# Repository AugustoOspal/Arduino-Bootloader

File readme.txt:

Comando para pull github.
Copiar las tres lineas y pegarlas en CMD

D:
cd "Pasantia 2021\Augusto Ospal\Arduino UNO bootloader"
git pull

Las hojas con los planos a imprimir de las plaquetas estan en cada una de las carpetas en las que corresponden

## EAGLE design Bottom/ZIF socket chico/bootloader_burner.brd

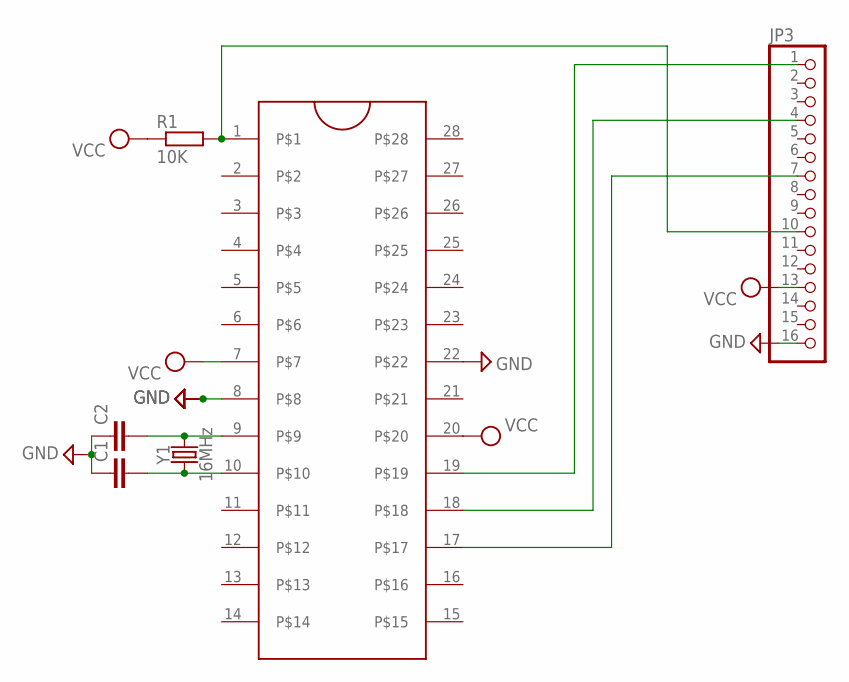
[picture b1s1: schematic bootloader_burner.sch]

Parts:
C1, C2: C-EU050-030X075; C050-030X075
J1: ZIFSOCKET-28-3"; DIL28-3-ZIF_SOCKET
JP3: PINHD-1X16; 1X16
R1: 10K; 0207/10
Y1: 16MHz; HC49US

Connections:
GND: C1.1, C2.1, J1.8, J1.22, JP3.16
unnamed: C2.2, J1.9, Y1.2
unnamed: C1.2, J1.10, Y1.1
PIN10ARDUINO: J1.1, JP3.10, R1.2
PIN11ARDUINO: J1.17, JP3.7
PIN12ARDUINO: J1.18, JP3.4
PIN13ARDUINO: J1.19, JP3.1
VCC: J1.7, J1.20, JP3.13, R1.1

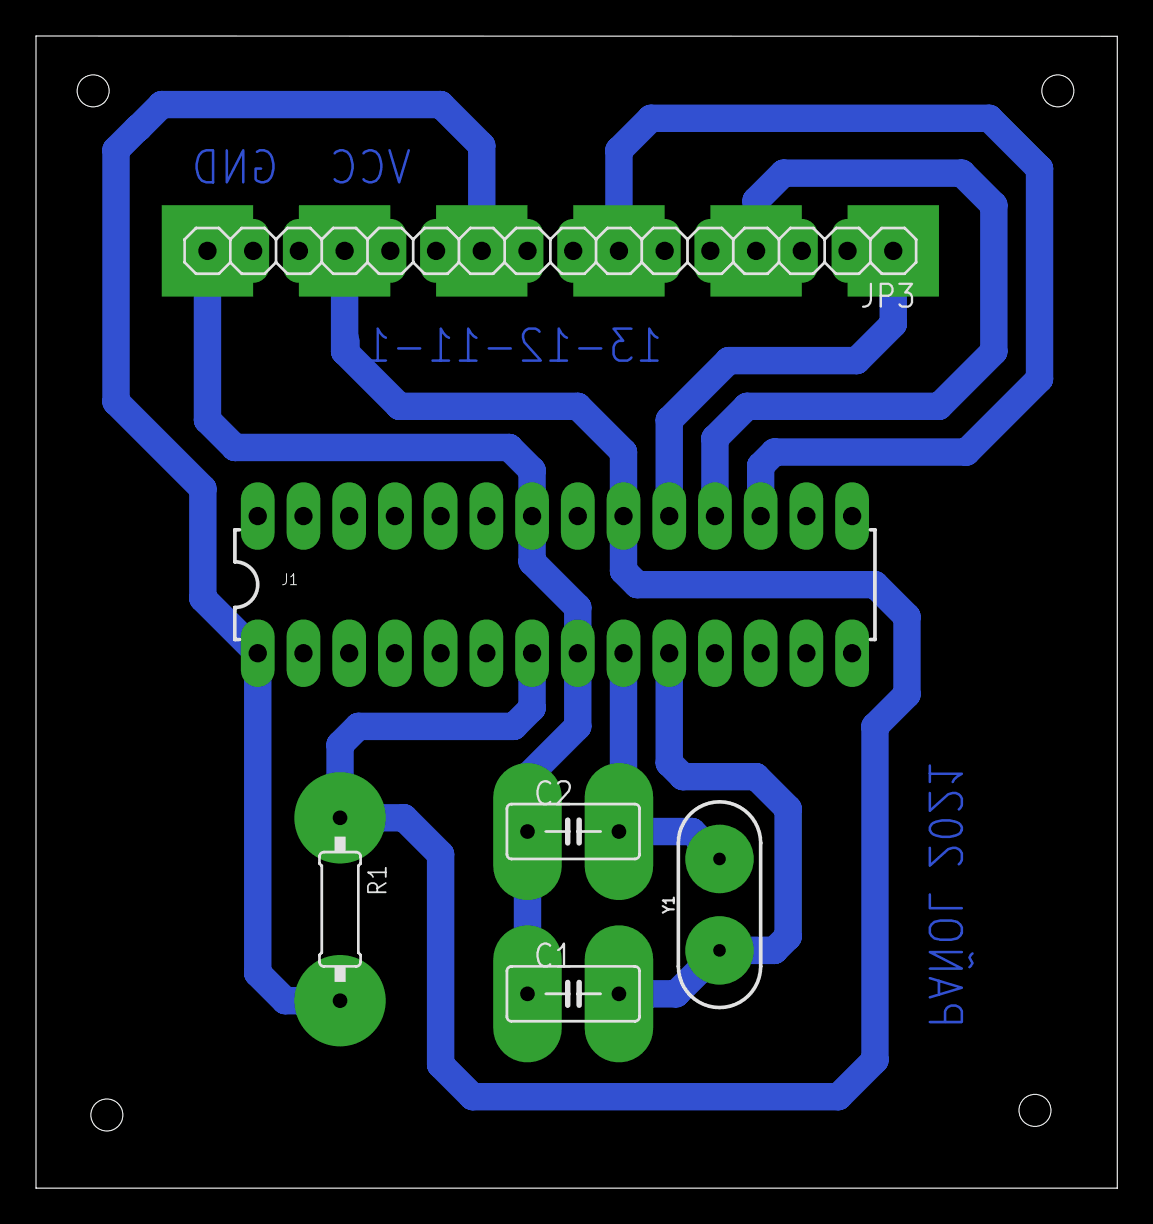
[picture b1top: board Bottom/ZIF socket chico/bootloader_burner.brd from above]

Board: 2 copper layers, 60.1 x 64.0 mm, 6 parts (0 on the bottom side), 8 nets.

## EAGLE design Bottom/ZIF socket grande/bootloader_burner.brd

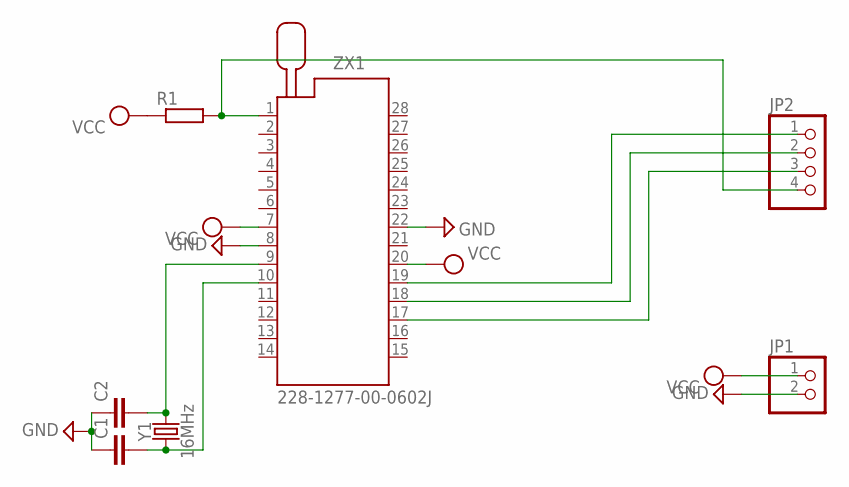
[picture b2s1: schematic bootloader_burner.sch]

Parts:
C1, C2: C-EU025-025X050; C025-025X050
JP1: PINHD-1X2; 1X02
JP2: PINHD-1X4; 1X04
R1: R-EU_0207/10; 0207/10
Y1: 16MHz; HC49US
ZX1: 228-1277-00-0602J

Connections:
GND: C1.1, C2.1, JP1.2, ZX1.8, ZX1.22
unnamed: C2.2, Y1.2, ZX1.9
unnamed: C1.2, Y1.1, ZX1.10
PIN_10_ARDUINO: JP2.4, R1.2, ZX1.1
PIN_11_ARDUINO: JP2.3, ZX1.17
PIN_12_ARDUINO: JP2.2, ZX1.18
PIN_13_ARDUINO: JP2.1, ZX1.19
VCC: JP1.1, R1.1, ZX1.7, ZX1.20

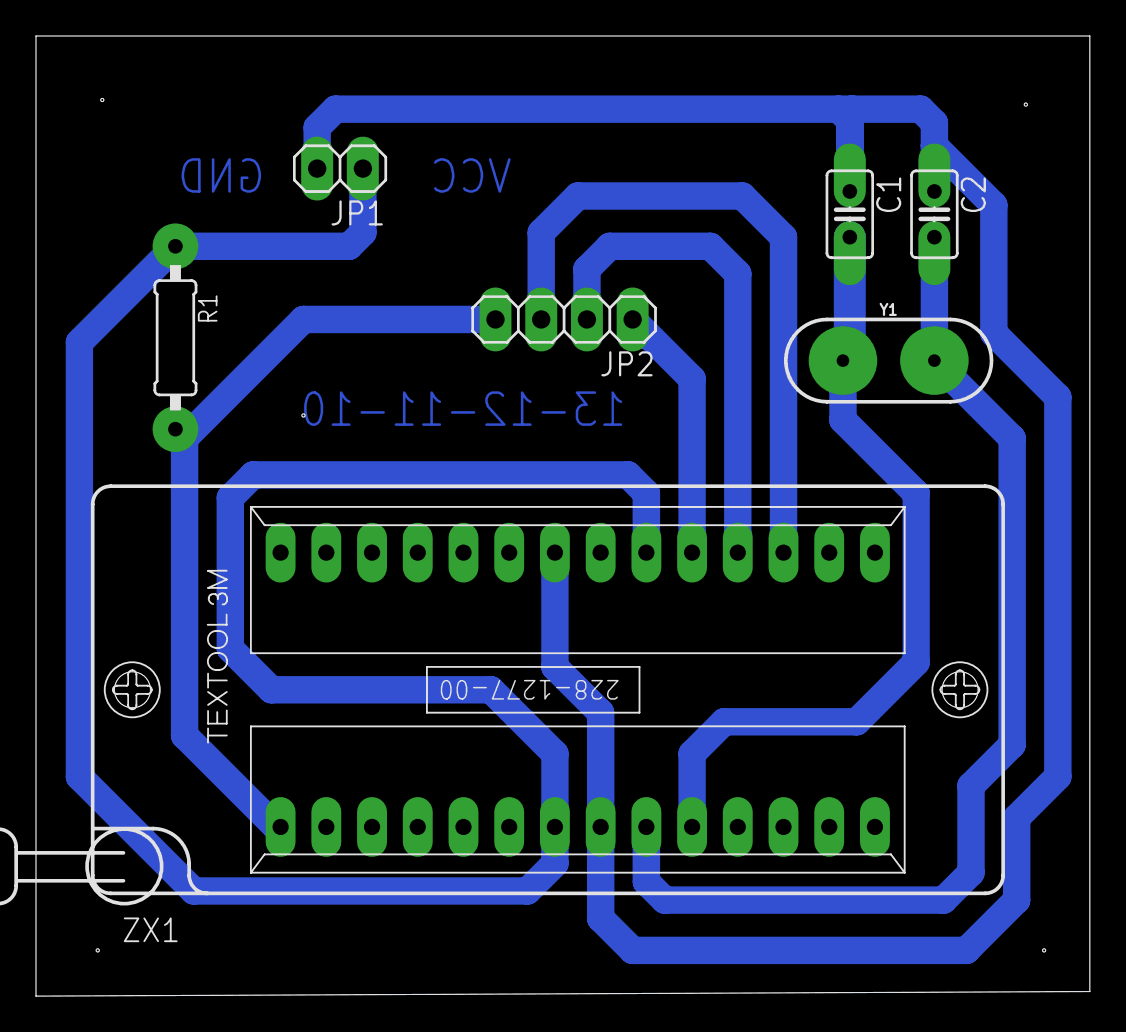
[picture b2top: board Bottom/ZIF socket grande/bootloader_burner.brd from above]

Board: 2 copper layers, 58.5 x 53.3 mm, 7 parts (0 on the bottom side), 8 nets.

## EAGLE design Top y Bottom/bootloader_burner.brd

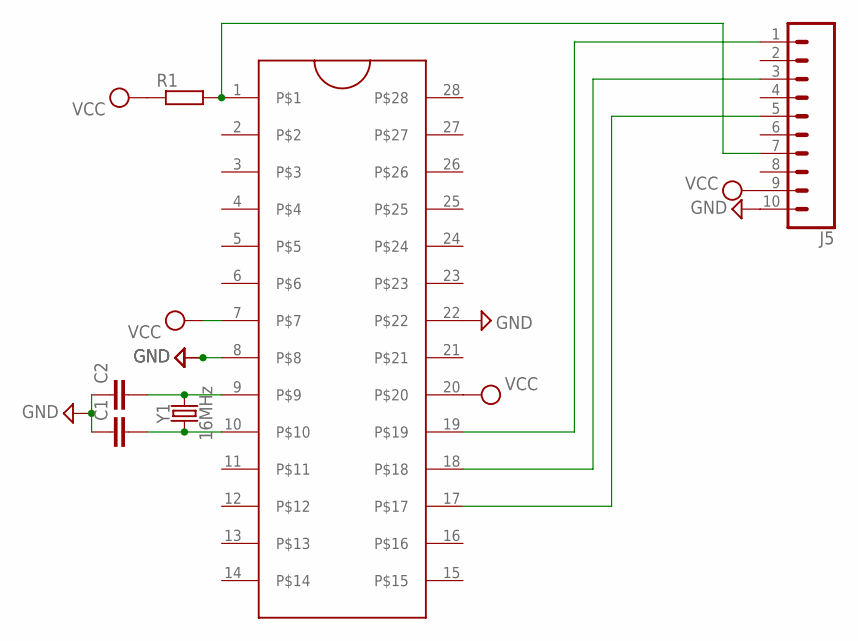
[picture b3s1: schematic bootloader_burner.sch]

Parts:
C1, C2: C-EU025-025X050; C025-025X050
J1: ZIFSOCKET-28-3"; DIL28-3-ZIF_SOCKET
J5: CONN_10"; 1X10
R1: R-EU_0207/10; 0207/10
Y1: 16MHz; HC49US

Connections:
GND: C1.1, C2.1, J1.8, J1.22, J5.10
unnamed: C2.2, J1.9, Y1.2
unnamed: C1.2, J1.10, Y1.1
PIN_10: J1.1, J5.7, R1.2
PIN_11: J1.17, J5.5
PIN_12: J1.18, J5.3
PIN_13: J1.19, J5.1
VCC: J1.7, J1.20, J5.9, R1.1

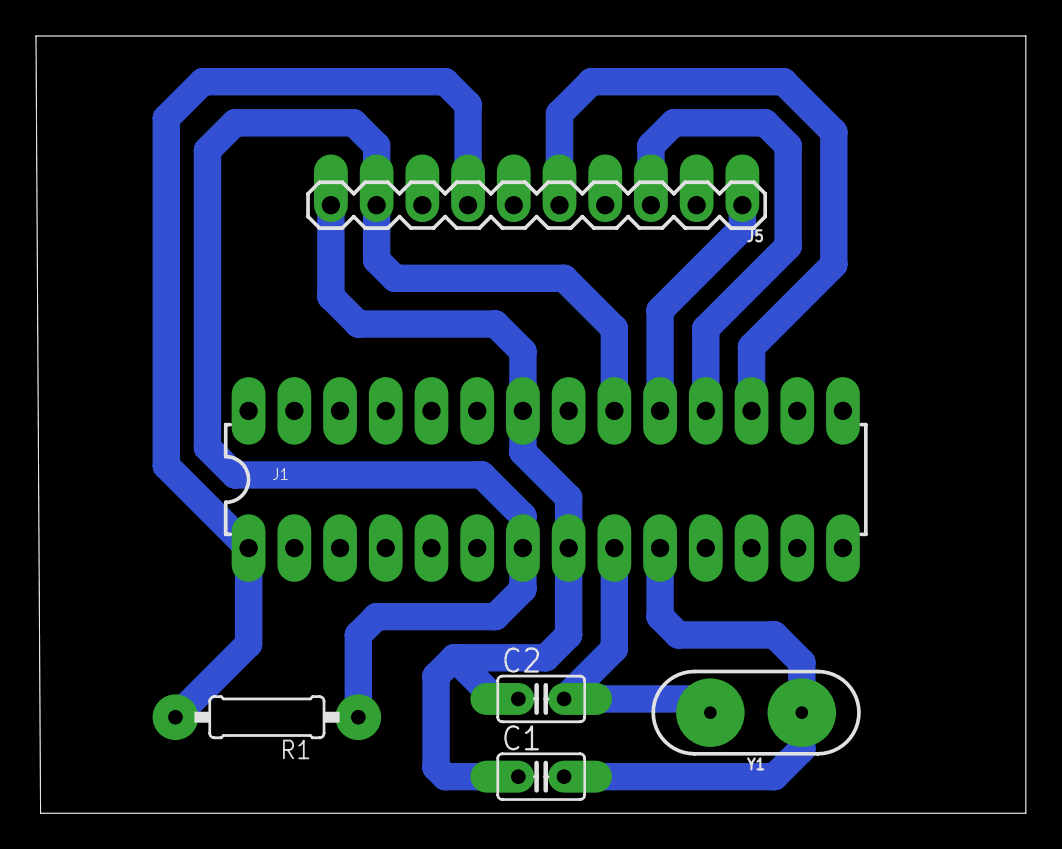
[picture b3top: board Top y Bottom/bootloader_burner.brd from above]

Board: 2 copper layers, 55.0 x 43.2 mm, 6 parts (0 on the bottom side), 8 nets.

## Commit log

2021-09-17 Version 1 probando
2021-09-29 Agrego los archivos
2021-09-30 Cambie la plaqueta para el zif socket chico para que queden ordenados los pines para conectar la plaqueta al Arduino
2021-09-30 Cambie el diseño de la plaqueta con zif socket grande para que queden ordenados los pines con los del Arduino. Tambien cambie el dieño de la plaqueta doble (que igual hay que cambiarla poque la graci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
2021-10-01 Borre un word repetido y un par de fotos de las plaquetas
2021-10-01 Agregue las fotos nuevas de las plaquetas y agregue la lista de componentes al word
2021-10-01 Agregue las dos plaquetas simples al word. Pase el word a pdf y lo uni con los planos a imprimir de los circuitos
2021-10-01 Cambie detalles
2021-10-01 Cambie el readme
2021-10-01 Agregue el pdf
2021-10-01 Cree el archivo pdf final donde estan todas las vistas como corresponden y listas para imprimir
2021-10-01 Agregue el pdf y las vistas normales de las plaquetas
2021-10-01 Borre un archivo y le cambie el nombre a otro
2021-10-01 Cambie el pdf
2021-10-01 Le cambie el nombre al archivo

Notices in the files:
parts and their libraries:
SparkFun-Connectors: Licensing: Creative Commons ShareAlike 4.0 International - https://creativecommons.org/licenses/by-sa/4.0
